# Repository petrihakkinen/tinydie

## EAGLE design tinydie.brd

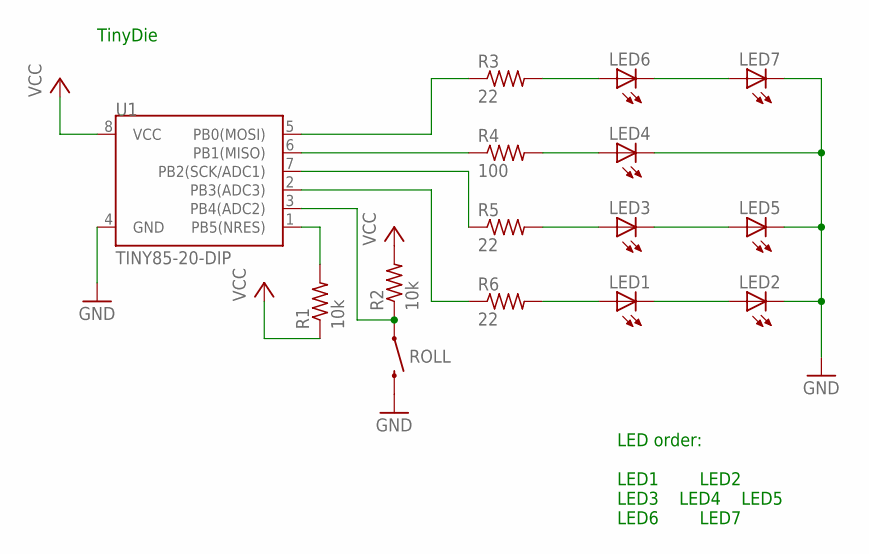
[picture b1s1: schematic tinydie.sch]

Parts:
LED1, LED2, LED3, LED4, LED5, LED6, LED7: LED3MM
R1, R2: 10k; 0207/7
R3, R5, R6: 22; 0207/7
R4: 100; 0207/7
ROLL: SWITCH-MOMENTARY-2; TACTILE_SWITCH_TALL
U1: TINY85-20-DIP; DIP08

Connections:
GND: LED2.K (C), LED4.K (C), LED5.K (C), LED7.K (C), ROLL.B2 (2), U1.4 (GND)
L3: LED3.K (C), LED5.A
LED6: LED6.K (C), LED7.A
unnamed: LED6.A, R3.2
unnamed: LED1.K (C), LED2.A
unnamed: LED3.A, R5.2
unnamed: LED1.A, R6.2
unnamed: LED4.A, R4.2
unnamed: R3.1, U1.5 (PB0(MOSI))
unnamed: R4.1, U1.6 (PB1(MISO))
unnamed: R5.1, U1.7 (PB2(SCK/ADC1))
unnamed: R6.1, U1.2 (PB3(ADC3))
unnamed: R2.1, ROLL.A2 (1), U1.3 (PB4(ADC2))
unnamed: R1.2, U1.1 (PB5(NRES))
VCC: R1.1, R2.2, U1.8 (VCC)

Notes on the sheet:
LED order: LED1 LED2 LED3 LED4 LED5 LED6 LED7
TinyDie

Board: 2 copper layers, 15 parts (0 on the bottom side), 15 nets, no tracks yet.

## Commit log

2016-05-17 Added files.

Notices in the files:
parts and their libraries:
SparkFun-DigitalIC: Licensing: CC v3.0 Share-Alike You are welcome to use this library for commercial purposes.
